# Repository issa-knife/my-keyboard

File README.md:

# Introduction

I decided to try my hand at designing a keyboard.

## Requirements

- Diodeless(cause SMD soldering/desoldering is pain)
- 36 keys
- MX switches(south facing)
- LED screens are optional but fun
- Support RP2040 (elite-pi or knock-offs, PINS should match), because cheap and popular.

- Reversible PCB

## Steps

- I first created a layout using [ergogen], I started with [ferris sweep] since feels familiar.(not sure how comfortable the layout will be with MX switches)
- Saw this cool repository called [sweeeeep/sweep36], choose this since it was 36 keys already, supported elite-pi, and bonus! LED screen!! 😎
- Using MCU/TRRS/LED footprints from that sweep36, now we build this keyboard.(not sure what to call it)
- Best part is the [QMK firmware] for the sweep36 is already created, so I will just use that directly with this board.
- Then use another awesome community tool in [kicad] called [freerouting]
- TADA! This is the final product.

> DISCLAIMER: I don't know anything, use this at your own risk I am not liable to anything.

[ergogen]: https://ergogen.cache.works/
[ferris sweep]: https://github.com/davidphilipbarr/Sweep
[sweeeeep/sweep36]: https://github.com/sadekbaroudi/sweep36
[freerouting]: https://github.com/freerouting/freerouting
[kicad]: https://www.kicad.org/
[QMK firmware]: https://github.com/sadekbaroudi/qmk_firmware/tree/master/keyboards/fingerpunch/sweeeeep

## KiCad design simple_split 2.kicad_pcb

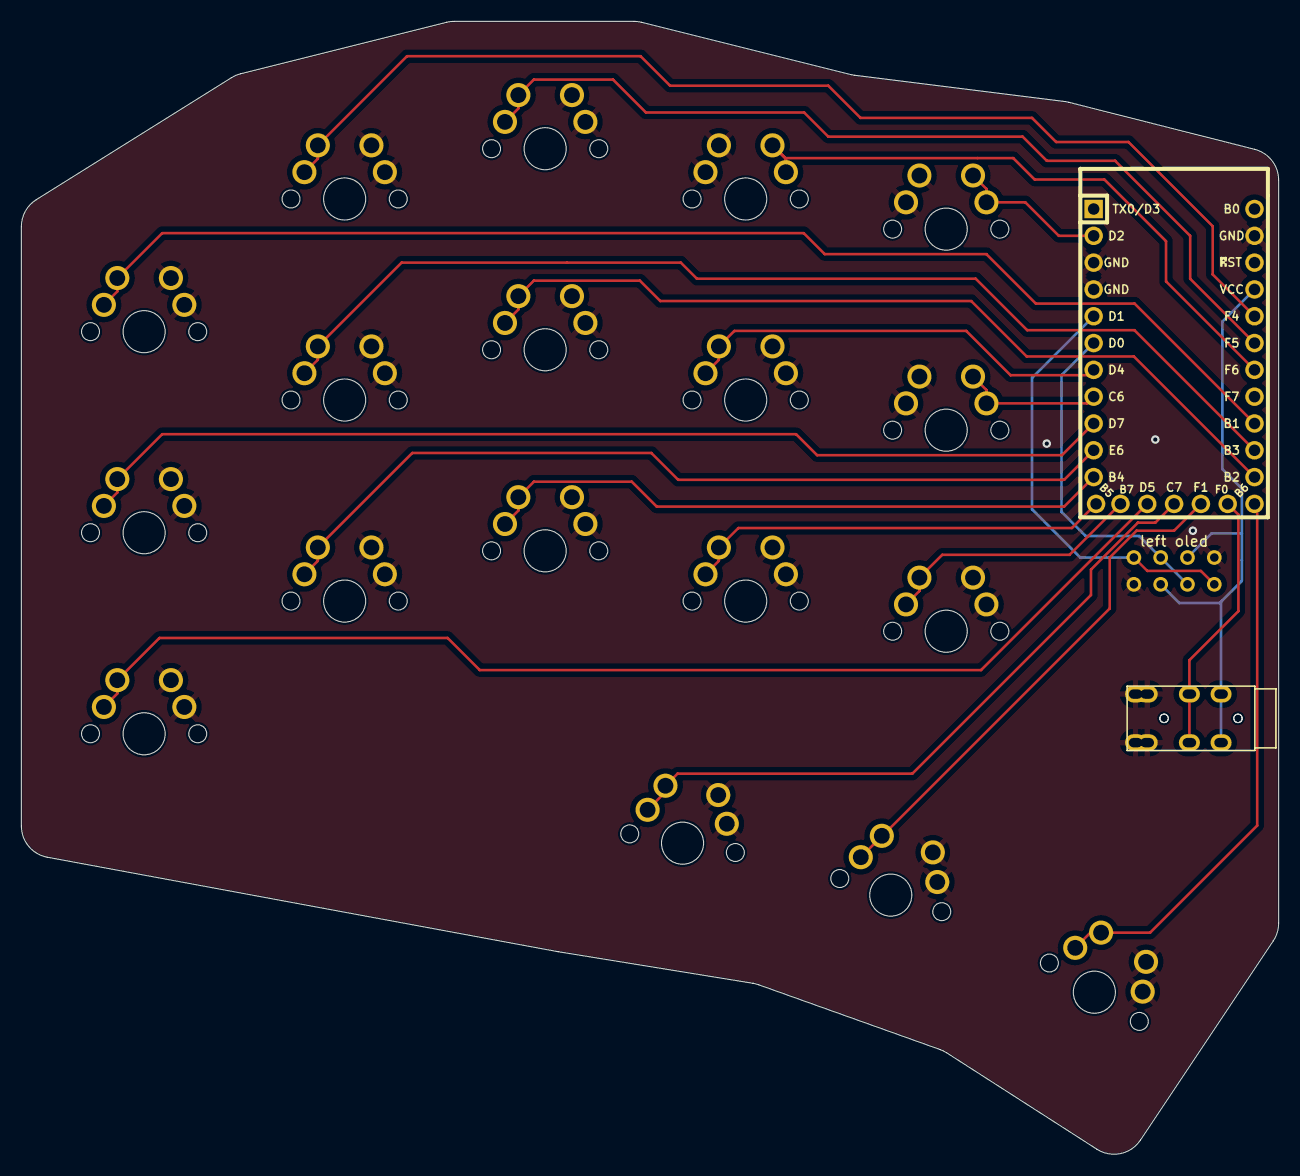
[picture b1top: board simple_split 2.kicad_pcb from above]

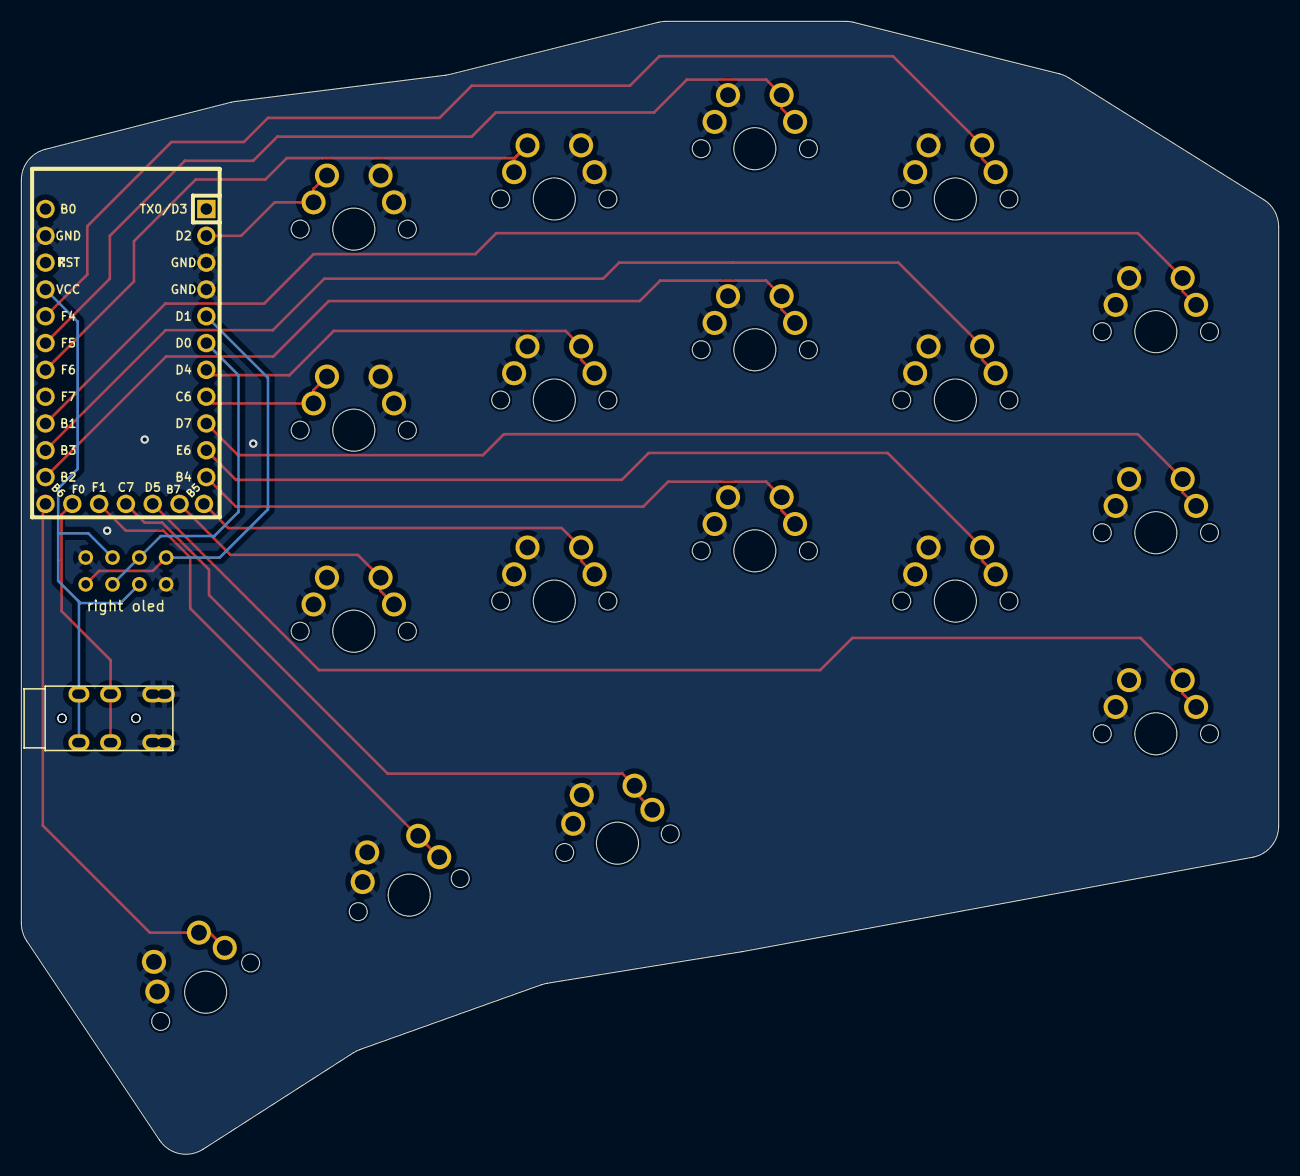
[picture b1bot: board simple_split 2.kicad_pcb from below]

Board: 2 copper layers, 119.1 x 107.3 mm, 23 parts (2 on the bottom side), 23 nets.

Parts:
J1, J2: AudioJack4dpb; TRRS-PJ-320A
OL1, OL2: OLED; OLED_v2
S1, S2, S3, S4, S5, S6, S7, S8, S9, S10, S11, S12, S13, S14, S15, S16, S17, S18: MX
U2: Elite-C

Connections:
Switch1: S3.1, S3.2, U2.16 (15/PB1)
Switch2: S6.1, S6.2, U2.20 (A3/PF4)
Switch3: S9.1, S9.2, U2.19 (A2/PF5)
Switch4: S12.1, S12.2, U2.18 (A1/PF6)
Switch5: S15.1, S15.2, U2.2 (RX1/PD2)
Switch6: S2.1, S2.2, U2.9 (6/PD7)
Switch7: S5.1, S5.2, U2.15 (14/PB3)
Switch8: S8.1, S8.2, U2.14 (16/PB2)
Switch9: S11.1, S11.2, U2.7 (4/PD4)
Switch10: S14.1, S14.2, U2.8 (5/PC6)
Switch11: S1.1, S1.2, U2.26 (D5)
Switch12: S4.1, S4.2, U2.10 (7/PE6)
Switch13: S7.1, S7.2, U2.11 (8/PB4)
Switch14: S10.1, S10.2, U2.12 (9/PB5)
Switch15: S13.1, S13.2, U2.25 (B7)
Switch16: S18.1, S18.2, U2.13 (10/PB6)
Switch17: S17.1, S17.2, U2.28 (F1)
Switch18: S16.1, S16.2, U2.27 (C7)
data: J1.3 (RING1), J2.3 (RING1), U2.29 (F0)
gnd: J1.1 (SLEEVE), J1.2 (TIP), J2.1 (SLEEVE), J2.2 (TIP), OL1.4 (GND), OL2.4 (GND), S1.1, S1.2, S2.1, S2.2, S3.1, S3.2, S4.1, S4.2, S5.1, S5.2, S6.1, S6.2, S7.1, S7.2, S8.1, S8.2, S9.1, S9.2, S10.1, S10.2, S11.1, S11.2, S12.1, S12.2, S13.1, S13.2, S14.1, S14.2, S15.1, S15.2, S16.1, S16.2, S17.1, S17.2, S18.1, S18.2, U2.3 (GND), U2.4 (GND), U2.23 (GND)
scl: OL1.2 (SCL), OL2.2 (SCL), U2.6 (3/PD0)
sda: OL1.1 (SDA), OL2.1 (SDA), U2.5 (2/PD1)
vcc: J1.4 (RING2), J2.4 (RING2), OL1.3 (VCC), OL2.3 (VCC), U2.21 (VCC)

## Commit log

2024-07-04 🎉 Initial commit
2024-08-09 ⬆️ V2 with ground plate
